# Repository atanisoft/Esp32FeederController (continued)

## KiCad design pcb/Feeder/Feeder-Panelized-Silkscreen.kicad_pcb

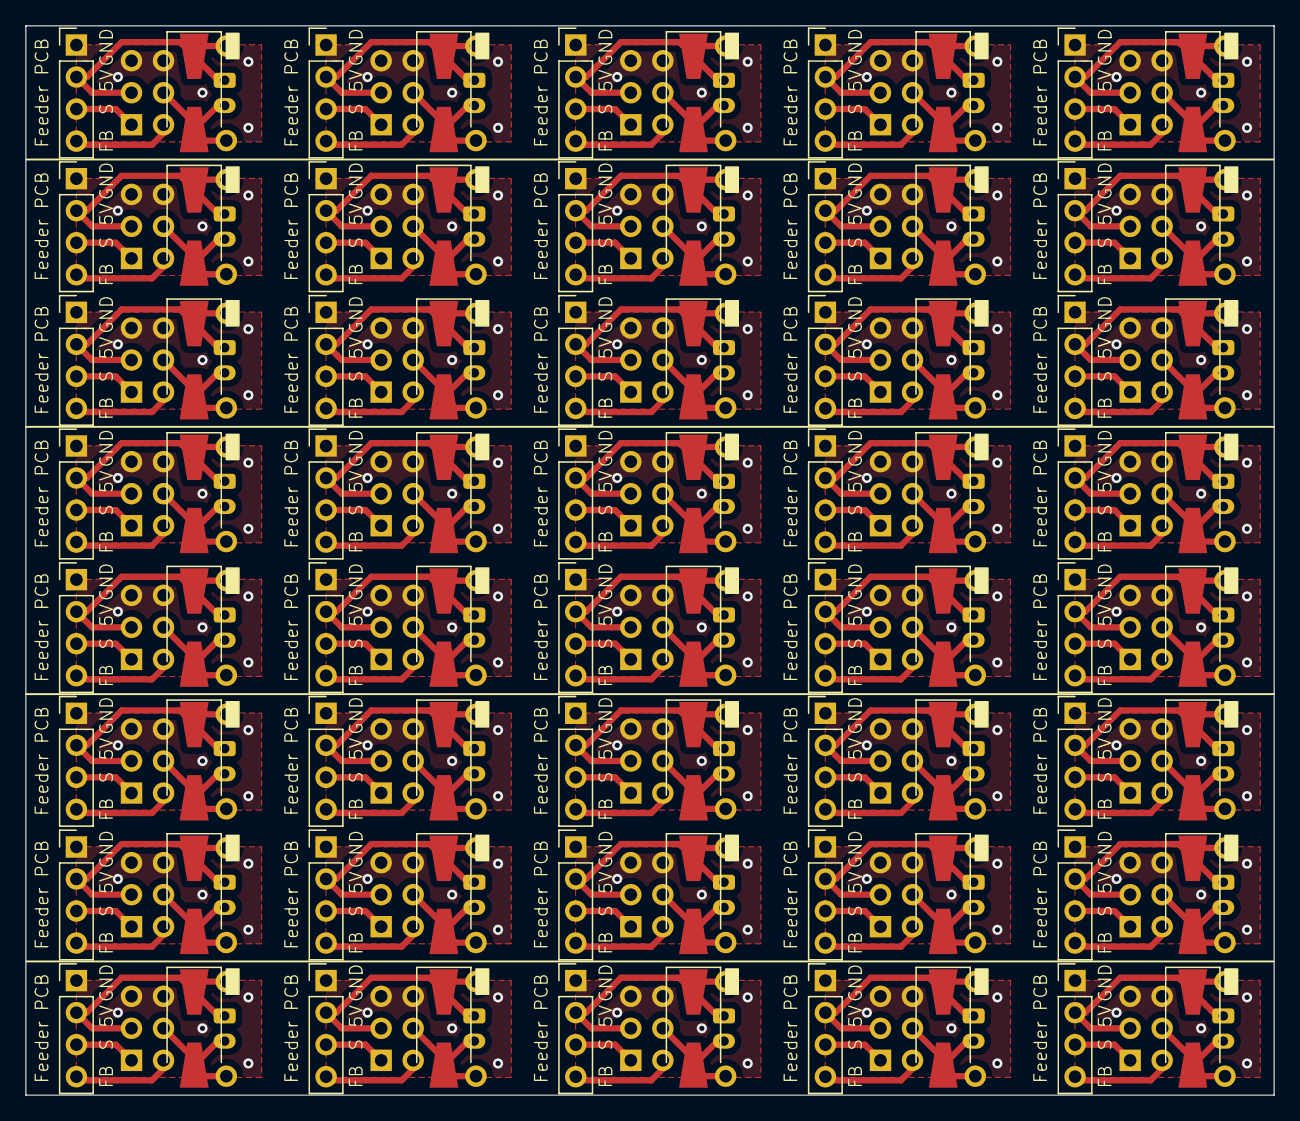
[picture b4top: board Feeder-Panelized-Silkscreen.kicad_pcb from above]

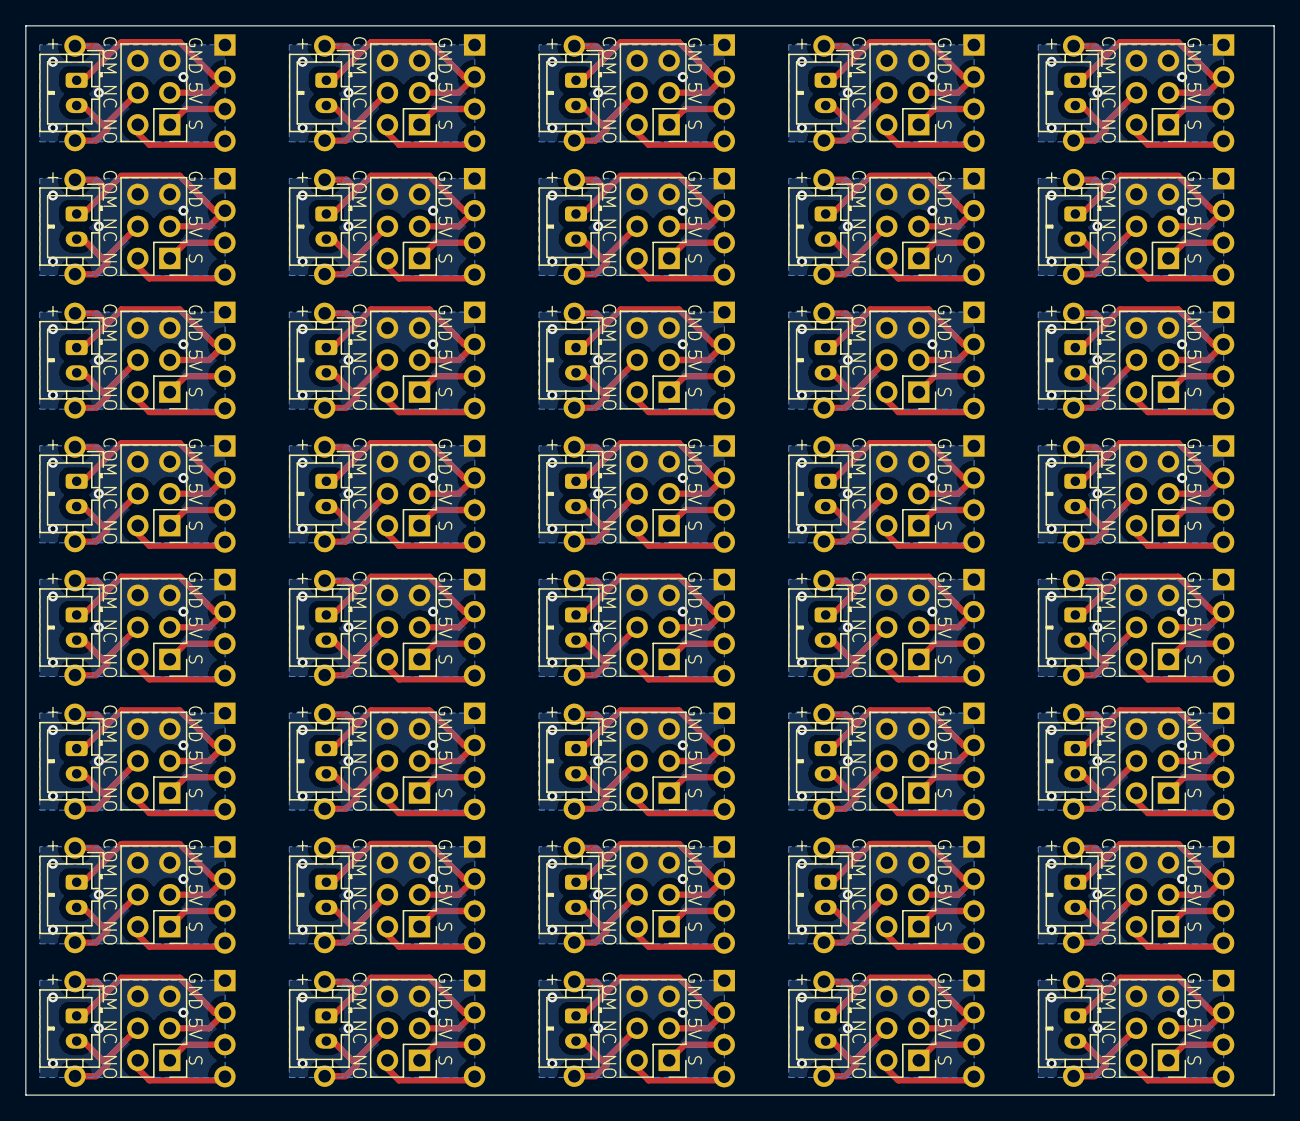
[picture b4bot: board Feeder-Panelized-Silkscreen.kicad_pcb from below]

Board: 2 copper layers, 99.0 x 84.8 mm, 200 parts (80 on the bottom side), 5 nets.

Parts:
D1, D3, D5, D7, D9, D11, D13, D15, D17, D19, D21, D23, D25, D27, D29, D31, D33, D35, D37, D39, D41, D43, D45, D47, D49, D51, D53, D55, D57, D59, D61, D63, D65, D67, D69, D71, D73, D75, D77, D79: 1N4001; D_SMA-SMB_Universal_Handsoldering
D2, D4, D6, D8, D10, D12, D14, D16, D18, D20, D22, D24, D26, D28, D30, D32, D34, D36, D38, D40, D42, D44, D46, D48, D50, D52, D54, D56, D58, D60, D62, D64, D66, D68, D70, D72, D74, D76, D78, D80: 1N4001; D_SMA-SMB_Universal_Handsoldering_Holes
J1, J4, J7, J10, J13, J16, J19, J22, J25, J28, J31, J34, J37, J40, J43, J46, J49, J52, J55, J58, J61, J64, J67, J70, J73, J76, J79, J82, J85, J88, J91, J94, J97, J100, J103, J106, J109, J112, J115, J118: Controller; PinHeader_1x04_P2.54mm_Vertical
J2, J5, J8, J11, J14, J17, J20, J23, J26, J29, J32, J35, J38, J41, J44, J47, J50, J53, J56, J59, J62, J65, J68, J71, J74, J77, J80, J83, J86, J89, J92, J95, J98, J101, J104, J107, J110, J113, J116, J119: N20; JST_PH_B2B-PH-K_1x02_P2.00mm_Vertical
J3, J6, J9, J12, J15, J18, J21, J24, J27, J30, J33, J36, J39, J42, J45, J48, J51, J54, J57, J60, J63, J66, J69, J72, J75, J78, J81, J84, J87, J90, J93, J96, J99, J102, J105, J108, J111, J114, J117, J120: Servo/Feedback; PinHeader_2x03_P2.54mm_Vertical

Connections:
+5V: D1.1 (K), D2.1 (K), D3.1 (K), D4.1 (K), D5.1 (K), D6.1 (K), D7.1 (K), D8.1 (K), D9.1 (K), D10.1 (K), D11.1 (K), D12.1 (K), D13.1 (K), D14.1 (K), D15.1 (K), D16.1 (K), D17.1 (K), D18.1 (K), D19.1 (K), D20.1 (K), D21.1 (K), D22.1 (K), D23.1 (K), D24.1 (K), D25.1 (K), D26.1 (K), D27.1 (K), D28.1 (K), D29.1 (K), D30.1 (K), D31.1 (K), D32.1 (K), D33.1 (K), D34.1 (K), D35.1 (K), D36.1 (K), D37.1 (K), D38.1 (K), D39.1 (K), D40.1 (K), D41.1 (K), D42.1 (K), D43.1 (K), D44.1 (K), D45.1 (K), D46.1 (K), D47.1 (K), D48.1 (K), D49.1 (K), D50.1 (K), D51.1 (K), D52.1 (K), D53.1 (K), D54.1 (K), D55.1 (K), D56.1 (K), D57.1 (K), D58.1 (K), D59.1 (K), D60.1 (K), D61.1 (K), D62.1 (K), D63.1 (K), D64.1 (K), D65.1 (K), D66.1 (K), D67.1 (K), D68.1 (K), D69.1 (K), D70.1 (K), D71.1 (K), D72.1 (K), D73.1 (K), D74.1 (K), D75.1 (K), D76.1 (K), D77.1 (K), D78.1 (K), D79.1 (K), D80.1 (K), J1.2, J2.1, J3.3, J4.2, J5.1, J6.3, J7.2, J8.1, J9.3, J10.2, J11.1, J12.3, J13.2, J14.1, J15.3, J16.2, J17.1, J18.3, J19.2, J20.1, J21.3, J22.2, J23.1, J24.3, J25.2, J26.1, J27.3, J28.2, J29.1, J30.3, J31.2, J32.1, J33.3, J34.2, J35.1, J36.3, J37.2, J38.1, J39.3, J40.2, J41.1, J42.3, J43.2, J44.1, J45.3, J46.2, J47.1, J48.3, J49.2, J50.1, J51.3, J52.2, J53.1, J54.3, J55.2, J56.1, J57.3, J58.2, J59.1, J60.3, J61.2, J62.1, J63.3, J64.2, J65.1, J66.3, J67.2, J68.1, J69.3, J70.2, J71.1, J72.3, J73.2, J74.1, J75.3, J76.2, J77.1, J78.3, J79.2, J80.1, J81.3, J82.2, J83.1, J84.3, J85.2, J86.1, J87.3, J88.2, J89.1, J90.3, J91.2, J92.1, J93.3, J94.2, J95.1, J96.3, J97.2, J98.1, J99.3, J100.2, J101.1, J102.3, J103.2, J104.1, J105.3, J106.2, J107.1, J108.3, J109.2, J110.1, J111.3, J112.2, J113.1, J114.3, J115.2, J116.1, J117.3, J118.2, J119.1, J120.3
/FEEDBACK: J1.4, J3.2, J4.4, J6.2, J7.4, J9.2, J10.4, J12.2, J13.4, J15.2, J16.4, J18.2, J19.4, J21.2, J22.4, J24.2, J25.4, J27.2, J28.4, J30.2, J31.4, J33.2, J34.4, J36.2, J37.4, J39.2, J40.4, J42.2, J43.4, J45.2, J46.4, J48.2, J49.4, J51.2, J52.4, J54.2, J55.4, J57.2, J58.4, J60.2, J61.4, J63.2, J64.4, J66.2, J67.4, J69.2, J70.4, J72.2, J73.4, J75.2, J76.4, J78.2, J79.4, J81.2, J82.4, J84.2, J85.4, J87.2, J88.4, J90.2, J91.4, J93.2, J94.4, J96.2, J97.4, J99.2, J100.4, J102.2, J103.4, J105.2, J106.4, J108.2, J109.4, J111.2, J112.4, J114.2, J115.4, J117.2, J118.4, J120.2
/N20-GND: D1.2 (A), D2.2 (A), D3.2 (A), D4.2 (A), D5.2 (A), D6.2 (A), D7.2 (A), D8.2 (A), D9.2 (A), D10.2 (A), D11.2 (A), D12.2 (A), D13.2 (A), D14.2 (A), D15.2 (A), D16.2 (A), D17.2 (A), D18.2 (A), D19.2 (A), D20.2 (A), D21.2 (A), D22.2 (A), D23.2 (A), D24.2 (A), D25.2 (A), D26.2 (A), D27.2 (A), D28.2 (A), D29.2 (A), D30.2 (A), D31.2 (A), D32.2 (A), D33.2 (A), D34.2 (A), D35.2 (A), D36.2 (A), D37.2 (A), D38.2 (A), D39.2 (A), D40.2 (A), D41.2 (A), D42.2 (A), D43.2 (A), D44.2 (A), D45.2 (A), D46.2 (A), D47.2 (A), D48.2 (A), D49.2 (A), D50.2 (A), D51.2 (A), D52.2 (A), D53.2 (A), D54.2 (A), D55.2 (A), D56.2 (A), D57.2 (A), D58.2 (A), D59.2 (A), D60.2 (A), D61.2 (A), D62.2 (A), D63.2 (A), D64.2 (A), D65.2 (A), D66.2 (A), D67.2 (A), D68.2 (A), D69.2 (A), D70.2 (A), D71.2 (A), D72.2 (A), D73.2 (A), D74.2 (A), D75.2 (A), D76.2 (A), D77.2 (A), D78.2 (A), D79.2 (A), D80.2 (A), J2.2, J3.4, J5.2, J6.4, J8.2, J9.4, J11.2, J12.4, J14.2, J15.4, J17.2, J18.4, J20.2, J21.4, J23.2, J24.4, J26.2, J27.4, J29.2, J30.4, J32.2, J33.4, J35.2, J36.4, J38.2, J39.4, J41.2, J42.4, J44.2, J45.4, J47.2, J48.4, J50.2, J51.4, J53.2, J54.4, J56.2, J57.4, J59.2, J60.4, J62.2, J63.4, J65.2, J66.4, J68.2, J69.4, J71.2, J72.4, J74.2, J75.4, J77.2, J78.4, J80.2, J81.4, J83.2, J84.4, J86.2, J87.4, J89.2, J90.4, J92.2, J93.4, J95.2, J96.4, J98.2, J99.4, J101.2, J102.4, J104.2, J105.4, J107.2, J108.4, J110.2, J111.4, J113.2, J114.4, J116.2, J117.4, J119.2, J120.4
/SERVO: J1.3, J3.1, J4.3, J6.1, J7.3, J9.1, J10.3, J12.1, J13.3, J15.1, J16.3, J18.1, J19.3, J21.1, J22.3, J24.1, J25.3, J27.1, J28.3, J30.1, J31.3, J33.1, J34.3, J36.1, J37.3, J39.1, J40.3, J42.1, J43.3, J45.1, J46.3, J48.1, J49.3, J51.1, J52.3, J54.1, J55.3, J57.1, J58.3, J60.1, J61.3, J63.1, J64.3, J66.1, J67.3, J69.1, J70.3, J72.1, J73.3, J75.1, J76.3, J78.1, J79.3, J81.1, J82.3, J84.1, J85.3, J87.1, J88.3, J90.1, J91.3, J93.1, J94.3, J96.1, J97.3, J99.1, J100.3, J102.1, J103.3, J105.1, J106.3, J108.1, J109.3, J111.1, J112.3, J114.1, J115.3, J117.1, J118.3, J120.1
GND: J1.1, J3.5, J3.6, J4.1, J6.5, J6.6, J7.1, J9.5, J9.6, J10.1, J12.5, J12.6, J13.1, J15.5, J15.6, J16.1, J18.5, J18.6, J19.1, J21.5, J21.6, J22.1, J24.5, J24.6, J25.1, J27.5, J27.6, J28.1, J30.5, J30.6, J31.1, J33.5, J33.6, J34.1, J36.5, J36.6, J37.1, J39.5, J39.6, J40.1, J42.5, J42.6, J43.1, J45.5, J45.6, J46.1, J48.5, J48.6, J49.1, J51.5, J51.6, J52.1, J54.5, J54.6, J55.1, J57.5, J57.6, J58.1, J60.5, J60.6, J61.1, J63.5, J63.6, J64.1, J66.5, J66.6, J67.1, J69.5, J69.6, J70.1, J72.5, J72.6, J73.1, J75.5, J75.6, J76.1, J78.5, J78.6, J79.1, J81.5, J81.6, J82.1, J84.5, J84.6, J85.1, J87.5, J87.6, J88.1, J90.5, J90.6, J91.1, J93.5, J93.6, J94.1, J96.5, J96.6, J97.1, J99.5, J99.6, J100.1, J102.5, J102.6, J103.1, J105.5, J105.6, J106.1, J108.5, J108.6, J109.1, J111.5, J111.6, J112.1, J114.5, J114.6, J115.1, J117.5, J117.6, J118.1, J120.5, J120.6

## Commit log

2022-03-18 Add periodic timer for heap monitoring. Moved feeder management code to FeederManager.hxx Added SocInfo during startup.
2022-03-18 Split and cleanup of FeederManager, GCodeServer/Client/etc.
2022-03-19 Adding servo movement control and initial implementation of retract/move.
2022-03-20 Add worker pool and clean up data types
2022-03-20 Fix up a few bugs in the GCode Client handling
2022-03-22 Split/rework Feeder integration to include a timer per feeder
2022-03-23 Integrate MCP23017 for feeder feedback.
    Shifted SCL from 22 to 21 (TTGO-T1 uses 22 for on-board LED).
2022-03-23 M115 bug fix
2022-03-24 Add initial PCB, not yet tested
2022-03-24 add correct pcb render
2022-03-25 Update PCB as below
    * Adjusted placement of mounting holes to line up with LumenPnP staging plate.
    * Added 2k4 P/U for SDA/SCL.
    * GND plane stitching
2022-03-25 Feeder servo control integration work.
    Feeders should now be able to advance/retract as expected when commands are received.
2022-03-25 Add option to auto-enable feeders on startup
2022-03-25 Add basic readme
2022-03-25 Include option to disable feedback from feeders
2022-03-26 Added a few DNP footprints for connecting two PCBs together using a single ESP32
2022-03-27 Initial re-creation of Feeder PCB using SMD diode and JST-PH connector for N20
2022-03-27 Update Feeder PCB to adjust footprints for clearances.
2022-03-28 Add CC-BY-NC-SA-4.0 tags to code
2022-03-28 Update LICENSE
2022-03-29 Fix compilation errors and M115 output.
2022-03-31 Ensure wifi SSID/PW do not exceed the buffer size.
2022-03-31 Fix PW copy
2022-04-03 Adjust readme to list missing features.
2022-04-09 Adding support for manual advance and slowing servo movement.
2022-05-22 Feeder - added optional THT diode footprint, repanelized
2022-05-22 Feeder - added optional THT diode footprint, repanelized (#1)
    * Feeder - added optional THT diode footprint, repanelized
    * Create IMPORTANT-ORDERING-INSTRUCTIONS.txt
2022-05-24 repanelized, increased board size with silk screen to reduce price
2022-05-25 re-panelized to use silk screen between small PCBs to reduce cost
2022-05-25 re-panelized to use silk screen between small PCBs to reduce cost (#3)
2022-06-16 recreated feeder PCB for new 0816 CAD design
2022-06-16 recreated feeder PCB for new 0816 CAD design (#5)
2022-07-12 Rearrange controller PCB files, removed Feeder PCB files
2022-07-12 Fix default hostname
2022-12-16 Correct core assignment.
2023-03-30 Migrating to IDF v5+
2023-03-30 Migrating to IDF v5+ (#7)
2023-04-01 Fix off-by-one error in feeder numbering.
    Fixes: https://github.com/atanisoft/Esp32FeederController/issues/9
2023-04-16 Exclude R3 and R9 from population.
    Upgrades files to KiCad 7.x.
    Fixes: https://github.com/atanisoft/Esp32FeederController/issues/10
